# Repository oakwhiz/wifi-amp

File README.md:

# wifi-amp
2.45 GHz Bidirectional Amplifier (uses TX power detection to trigger RF switch)

Use at your own risk

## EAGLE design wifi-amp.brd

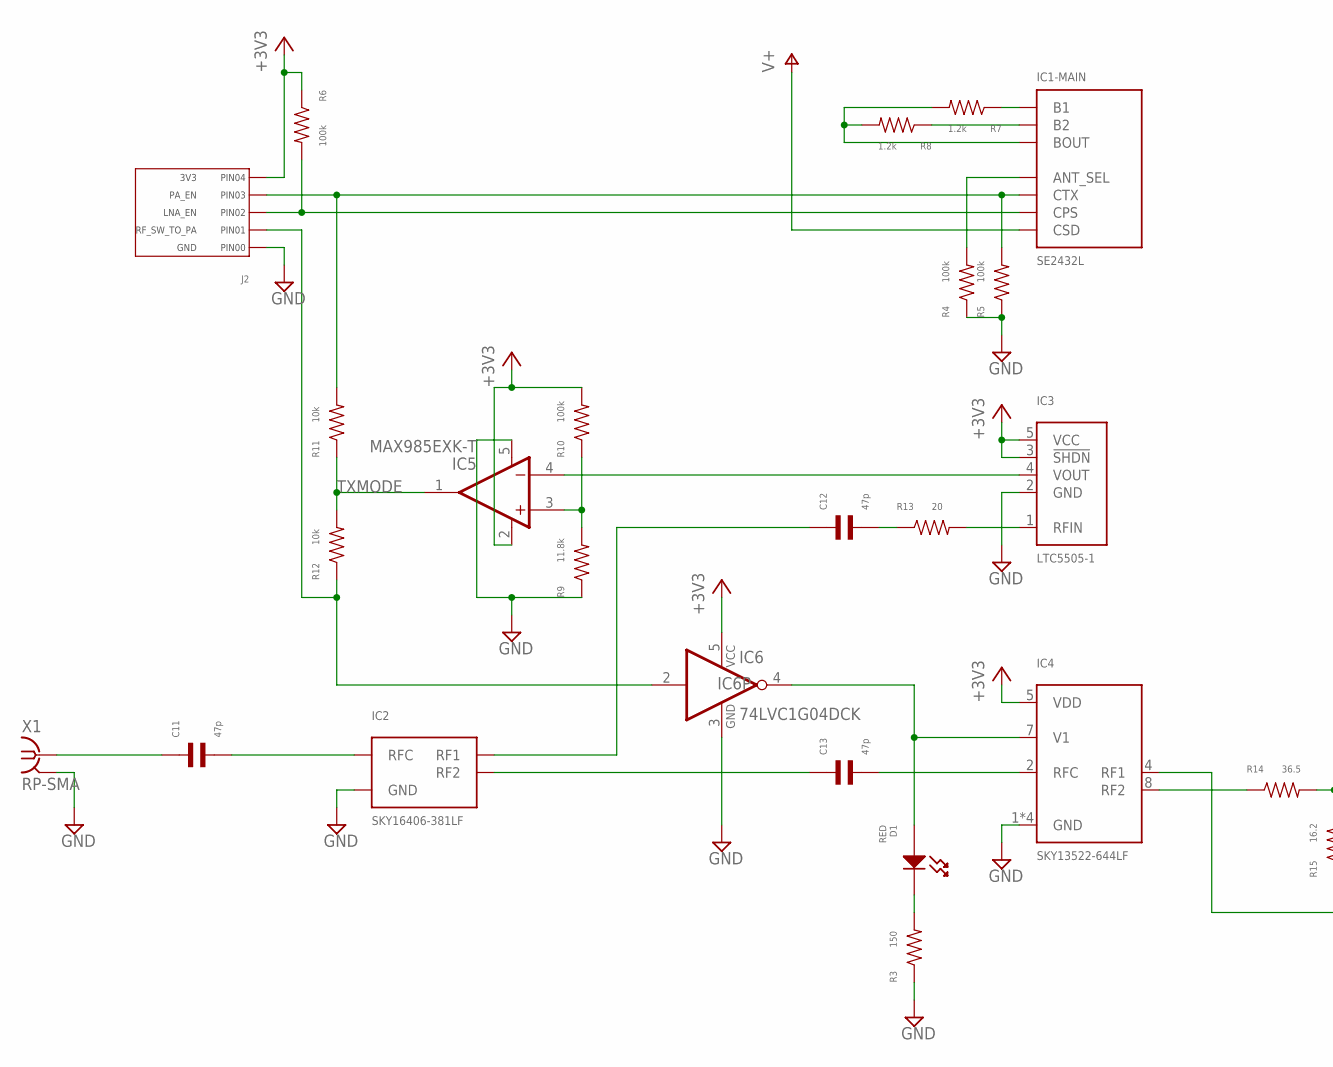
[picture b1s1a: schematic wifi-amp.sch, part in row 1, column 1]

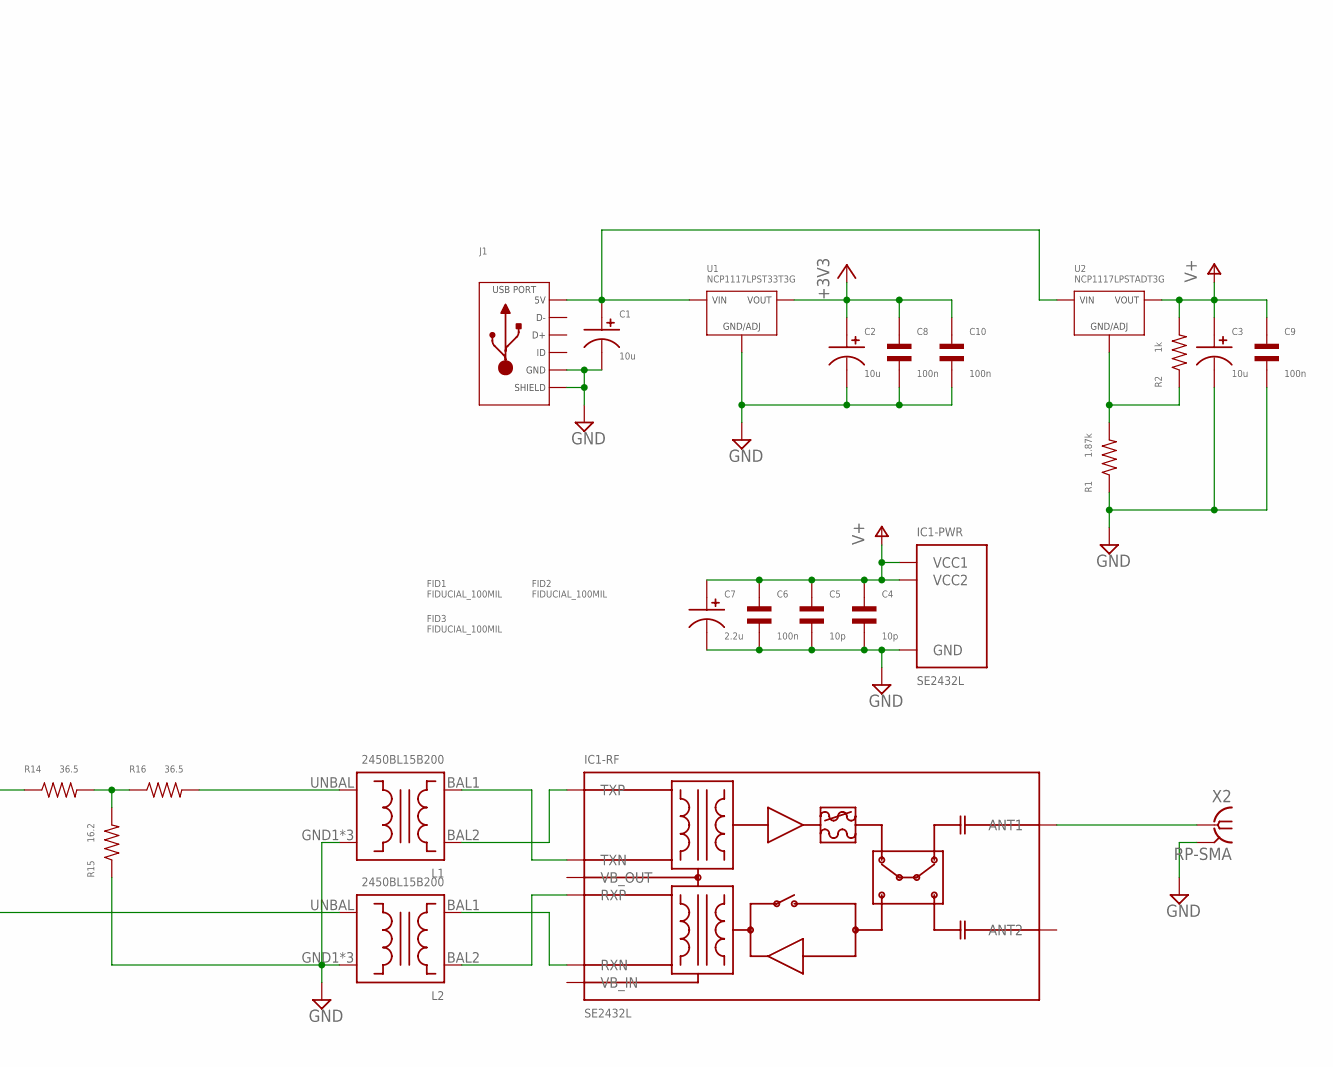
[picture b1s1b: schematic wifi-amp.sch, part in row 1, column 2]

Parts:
C1, C2, C3: 10u; CP4MM
C4, C5: 10p; C0402
C6, C8, C9, C10: 100n; C0402
C7: 2.2u; CP4MM
C11, C12, C13: 47p; C0402
D1: RED; LED0603
FID1, FID2, FID3: FIDUCIAL_100MIL
IC1: SE2432L; 24QFN
IC2: SKY16406-381LF; DFN6
IC3: LTC5505-1; SOT23-5
IC4: SKY13522-644LF; QFN8
IC5: MAX985EXK-T; SC70-5L
IC6: 74LVC1G04DCK; SC70-5
J1: USB_MICRO_RIGHT; MICROUSB-RIGHT
J2: HEADER_01X05_PTH_2.54MM; PTH_2.54MM_01X05
L1, L2: 2450BL15B200
R1: 1.87k; R0805; TOLERANCE 1%
R2: 1k; R0805; TOLERANCE 1%
R3: 150; R0402; TOLERANCE 1%
R4, R5, R6: 100k; R0402
R7, R8: 1.2k; R0402; TOLERANCE 1%
R9: 11.8k; R0402; TOLERANCE 1%
R10: 100k; R0402; TOLERANCE 1%
R11, R12: 10k; R0402
R13: 20; R0402; TOLERANCE 1%
R14, R16: 36.5; R0402; TOLERANCE 1%
R15: 16.2; R0402; TOLERANCE 1%
U1: NCP1117LPST33T3G; SOT-223-3
U2: NCP1117LPSTADT3G; SOT-223-3
X1, X2: RP-SMA; BU-SMA-H

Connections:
+3V3: C2.P$1, C8.P$1, C10.P$1, IC3.3 (!SHDN), IC3.5 (VCC), IC4.5 (VDD), IC5.2 (V+), IC6.5 (VCC), J2.P$5 (PIN4), R6.P$1, R10.P$2, U1.P$1 (VOUT), U1.P$3 (VOUT)
+5V: C1.P$1, J1.1 (5V), U1.P$4 (VIN), U2.P$4 (VIN)
ANT_SEL: IC1.ANT_SEL, R4.P$2
CPS: IC1.CPS, J2.P$3 (PIN2), R6.P$2
CTX: IC1.CTX, J2.P$4 (PIN3), R5.P$2, R11.P$2
GND: C1.P$2, C2.P$2, C3.P$2, C4.P$2, C5.P$2, C6.P$2, C7.P$2, C8.P$2, C9.P$2, C10.P$2, IC1.GND1 (GND), IC1.GND2 (GND), IC1.GND3 (GND), IC1.GND4 (GND), IC1.GND5 (GND), IC1.GND6 (GND), IC1.GND7 (GND), IC1.GND8 (GND), IC1.GND9 (GND), IC1.GND10 (GND), IC2.GND1 (GND), IC2.GND2 (GND), IC2.GND3 (GND), IC2.GNDP (GND), IC3.2 (GND), IC4.1 (GND), IC4.3 (GND), IC4.6 (GND), IC4.EP (GND), IC5.5 (V-), IC6.3 (GND), J1.5 (GND), J1.S1 (SLD), J1.S2 (SLD), J1.S3 (SLD), J1.S4 (SLD), J1.S5 (SLD), J1.S6 (SLD), J1.S7 (SLD), J1.S8 (SLD), J2.P$1 (PIN0), L1.GND1 (GND), L1.GND2 (GND), L1.GND3 (GND), L2.GND1 (GND), L2.GND2 (GND), L2.GND3 (GND), R1.P$1, R3.P$1, R4.P$1, R5.P$1, R9.P$1, R15.P$1, U1.P$2 (GND/ADJ), X1.2, X1.3 (2), X1.4 (2), X1.5 (2), X2.2, X2.3 (2), X2.4 (2), X2.5 (2)
unnamed: C11.P$1, X1.1
unnamed: R1.P$2, R2.P$1, U2.P$2 (GND/ADJ)
unnamed: D1.CATHODE, R3.P$2
unnamed: IC1.B1, R7.P$1
unnamed: IC1.B2, R8.P$1
unnamed: IC1.BOUT, R7.P$2, R8.P$2
unnamed: IC1.ANT1, X2.1
unnamed: IC3.1 (RFIN), R13.P$2
unnamed: IC1.TXN, L1.BAL1
unnamed: IC1.TXP, L1.BAL2
unnamed: IC1.RXP, L2.BAL2
unnamed: IC1.RXN, L2.BAL1
unnamed: C11.P$2, IC2.RFC
unnamed: C12.P$2, R13.P$1
unnamed: IC4.4 (RF1), L2.UNBAL
unnamed: C12.P$1, IC2.RF1
unnamed: C13.P$1, IC2.RF2
unnamed: R14.P$2, R15.P$2, R16.P$1
unnamed: IC3.4 (VOUT), IC5.4 (-IN)
unnamed: IC5.3 (+IN), R9.P$2, R10.P$1
unnamed: L1.UNBAL, R16.P$2
unnamed: IC4.8 (RF2), R14.P$1
unnamed: C13.P$2, IC4.2 (RFC)
unnamed: D1.ANODE, IC4.7 (V1), IC6.4 (O)
RF_SW_TO_PA: IC6.2 (I), J2.P$2 (PIN1), R12.P$1
TXMODE: IC5.1 (OUT), R11.P$1, R12.P$2
V+: C3.P$1, C4.P$1, C5.P$1, C6.P$1, C7.P$1, C9.P$1, IC1.CSD, IC1.VCC1, IC1.VCC2, R2.P$2, U2.P$1 (VOUT), U2.P$3 (VOUT)

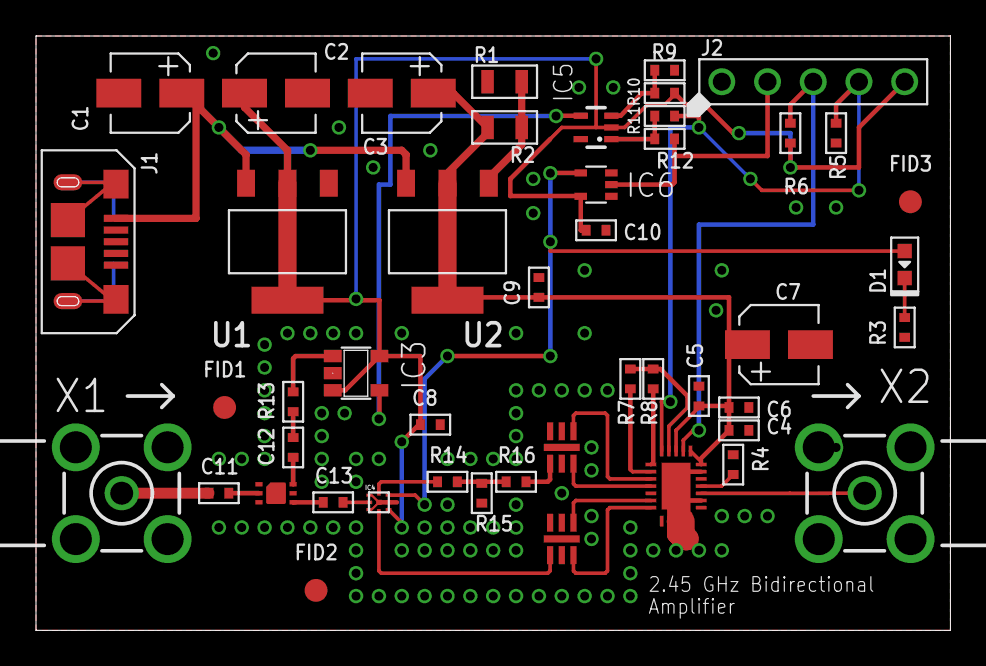
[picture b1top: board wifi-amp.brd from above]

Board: 2 copper layers, 50.8 x 33.0 mm, 47 parts (0 on the bottom side), 33 nets.

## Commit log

2016-05-05 Added files via upload
